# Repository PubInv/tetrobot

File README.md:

# gluss
An attempt to build metamorphic robots based on linear actuators. You probably want to go [https://pubinv.github.io/tetrobot/](https://pubinv.github.io/tetrobot/) first.

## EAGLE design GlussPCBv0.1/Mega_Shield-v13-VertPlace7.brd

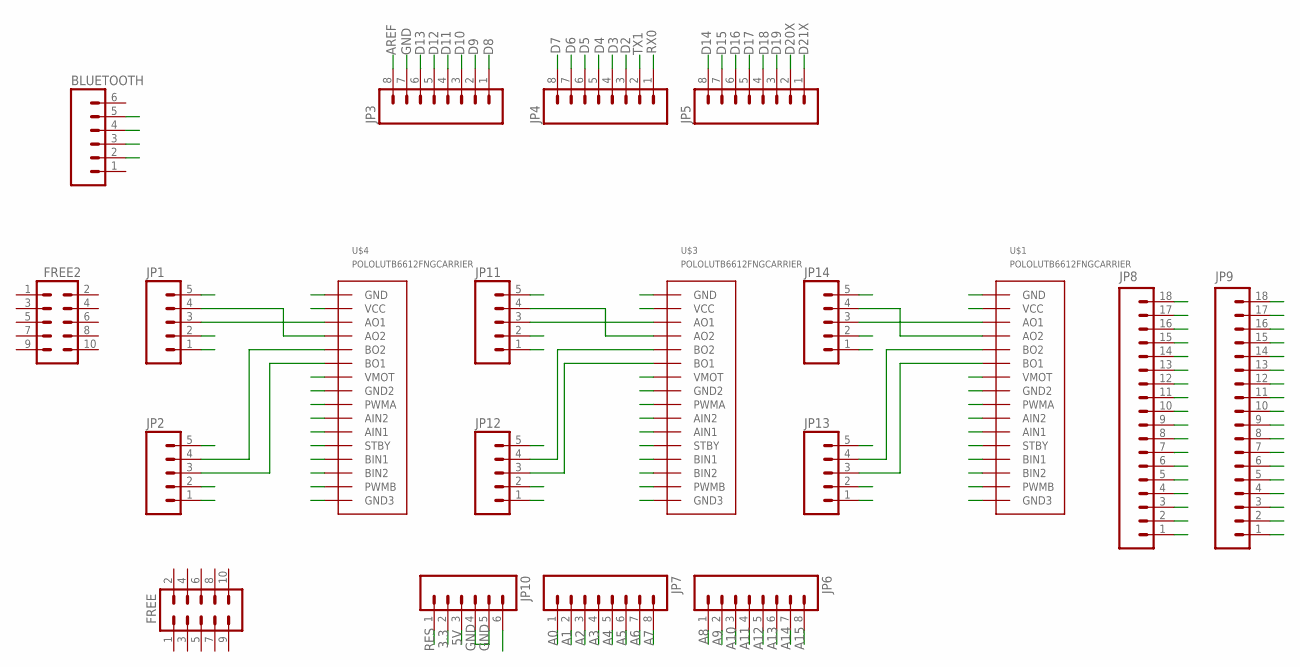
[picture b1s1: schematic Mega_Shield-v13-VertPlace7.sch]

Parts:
BLUETOOTH: M06FEMALE_LOCK; 1X06_FEMALE_LOCK.010
FREE, FREE2: M05X2NO_SILK; 2X5_NOSILK
JP1, JP2, JP11, JP12, JP13, JP14: M05LOCK; 1X05_LOCK
JP3, JP4, JP5, JP6, JP7: M08LOCK; 1X08_LOCK
JP8, JP9: M18_; 1X18
JP10: M06LOCK; 1X06_LOCK
U$1, U$3, U$4: POLOLUTB6612FNGCARRIER; THROUGHHOLECARRIER

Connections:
3.3: JP10.2
5V: BLUETOOTH.5, JP1.5, JP2.5, JP8.18, JP9.18, JP10.3, JP11.5, JP12.5, JP13.5, JP14.5, U$1.2 (VCC), U$1.12 (STBY), U$3.2 (VCC), U$3.12 (STBY), U$4.2 (VCC), U$4.12 (STBY)
A0: JP7.1, JP14.2
A1: JP7.2, JP13.2
A2: JP7.3, JP11.2
A3: JP7.4, JP12.2
A4: JP1.2, JP7.5
A5: JP2.2, JP7.6
A6: JP7.7
A7: JP7.8
A8: JP6.1
A9: JP6.2
A10: JP6.3
A11: JP6.4
A12: JP6.5
A13: JP6.6
A14: JP6.7
A15: JP6.8
AREF: JP3.8
D2: JP4.3, U$1.9 (PWMA)
D3: JP4.4, U$1.15 (PWMB)
D4: JP4.5, U$3.9 (PWMA)
D5: JP4.6, U$3.15 (PWMB)
D6: JP4.7, U$4.9 (PWMA)
D7: JP4.8, U$4.15 (PWMB)
D8: JP3.1
D9: JP3.2
D10: JP3.3
D11: JP3.4
D12: BLUETOOTH.2, JP3.5
D13: BLUETOOTH.3, JP3.6
D14: JP5.8
D15: JP5.7
D16: JP5.6
D17: JP5.5
D18: JP5.4
D19: JP5.3
D20X: JP5.2
D21X: JP5.1
D22: JP8.17
D23: JP9.17
D24: JP8.16
D25: JP9.16
D26: JP8.15
D27: JP9.15
D28: JP8.14
D29: JP9.14
D30: JP8.13
D31: JP9.13
D32: JP8.12
D33: JP9.12
D34: JP8.11
D35: JP9.11
D36: JP8.10
D37: JP9.10
D38: JP8.9
D40: JP8.8
D41: JP9.8
D42: JP8.7, U$4.14 (BIN2)
D43: JP9.7, U$4.13 (BIN1)
D44: JP8.6, U$4.10 (AIN2)
D45: JP9.6, U$4.11 (AIN1)
D46: JP8.5, U$3.14 (BIN2)
D47: JP9.5, U$3.13 (BIN1)
D48: JP8.4, U$3.10 (AIN2)
D49: JP9.4, U$3.11 (AIN1)
D50: JP8.3, U$1.14 (BIN2)
D51: JP9.3, U$1.13 (BIN1)
D52: JP8.2, U$1.10 (AIN2)
D53: JP9.2, U$1.11 (AIN1)
GND: BLUETOOTH.4, JP1.1, JP2.1, JP3.7, JP8.1, JP9.1, JP10.4, JP10.5, JP11.1, JP12.1, JP13.1, JP14.1, U$1.1 (GND), U$1.8 (GND2), U$1.16 (GND3), U$3.1 (GND), U$3.8 (GND2), U$3.16 (GND3), U$4.1 (GND), U$4.8 (GND2), U$4.16 (GND3)
unnamed: JP14.3, U$1.3 (AO1)
unnamed: JP14.4, U$1.4 (AO2)
unnamed: JP13.3, U$1.6 (BO1)
unnamed: JP13.4, U$1.5 (BO2)
unnamed: JP11.3, U$3.3 (AO1)
unnamed: JP12.3, U$3.6 (BO1)
unnamed: JP12.4, U$3.5 (BO2)
unnamed: JP11.4, U$3.4 (AO2)
unnamed: JP1.3, U$4.3 (AO1)
unnamed: JP1.4, U$4.4 (AO2)
unnamed: JP2.3, U$4.6 (BO1)
unnamed: JP2.4, U$4.5 (BO2)
RES: JP10.1
RX0: JP4.1
TX1: JP4.2
VIN: JP10.6, U$1.7 (VMOT), U$3.7 (VMOT), U$4.7 (VMOT)

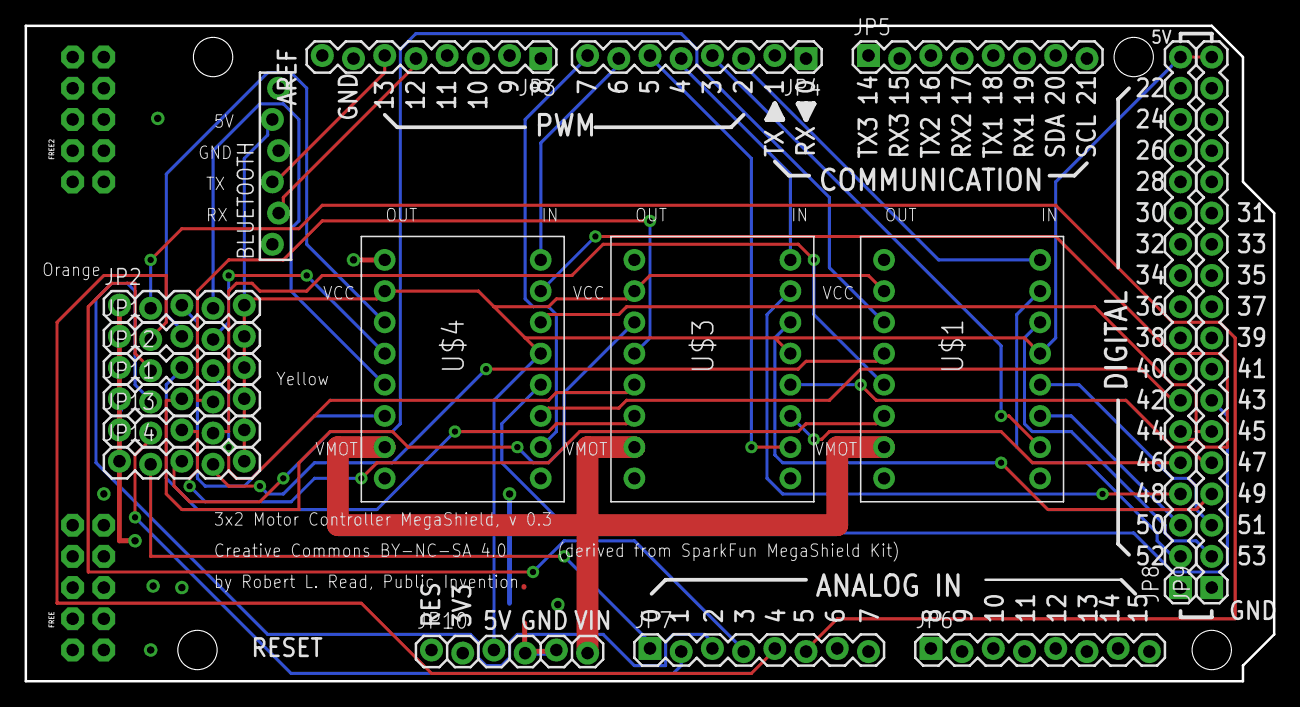
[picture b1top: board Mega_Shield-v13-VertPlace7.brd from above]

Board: 2 copper layers, 101.6 x 53.3 mm, 20 parts (0 on the bottom side), 41 nets.

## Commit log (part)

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2015-12-17 initial code for Arduino Mega
2015-12-20 finally have pure bluetooth working
2015-12-20 got the multiple thing working
2016-01-13 significant improvement
2016-01-13 more robust code to handle failing actuators
2016-03-01 Adding latest driver file, Makefile, Emacs Lisp control file, and bracket 3D printer files
2016-03-02 initial debug version of lisp interpreation of arduino output working
2016-03-02 improvements in status reporting and robustness of processing
2016-03-03 serious progress on simple s-expr library
2016-03-03 trying to move S-Expr
2016-03-04 supporing individual movement
2016-03-04 adding small example of positional operation
2016-03-05 significant progress on command convenience
2016-03-05 adding unique ids to calls and becoming more LISPy
2016-03-06 AWESOME--dance routine now allows series of steps across multiple controllers
2016-03-07 working through bug in value_i in S-Expr
2016-03-07 trying to get p function to work properly
2016-03-09 trouble with magit
2016-03-09 latest changes
2016-03-09 Test commit
2016-03-09 trivial change
2016-03-09 problems with magit
2016-03-09 drastic improvements to the way status is handeld
2016-03-10 New Poses
2016-03-10 adding .gitignore for Arduino complilation
2016-03-10 commiting pose
2016-03-11 adding scad
2016-03-11 new battery holder, first draft
2016-03-11 lots of movement but not walking, electronically buggy
2016-03-17 Forgot to actualy call del, now fixed!
2016-03-17 now walking, but very poorly
2016-03-18 Increaing baud rate to 19200, can't seem to go higher
2016-03-19 Major Milestone: move-forward now moves forward about 6" in 90 seconds
2016-03-20 turing left now works, although poorly
2016-03-20 added mirror function, though have not broadly employed it yet.
2016-03-23 fixing silly mistakes in mirroring
2016-03-24 mirorring working and turning working beautifully (45 degrees)
2016-03-24 slightly better move-forward routine
2016-03-24 slight improvements to walking
2016-03-24 major progress
2016-04-12 Create gh-pages branch via GitHub
2016-04-12 referencing public site
2016-04-12 updating before move to gh-pages
2016-04-12 removing gcoce from git control
2016-04-12 initial publication; half-baked
2016-04-13 Lots improvements
2016-04-14 improving photos and adding reference to issues
2016-04-15 Adding Table of Contents
2016-04-15 forgot to add this
2016-04-15 adding issues
2016-04-16 adding Eagle Files
2016-04-20 minor improvements
2016-04-20 changing to jekyll
2016-04-20 Touching
2016-04-20 adding empty
2016-04-20 yeah boy
2016-04-20 remvoing obsolete file
2016-04-20 fixing repo;
2016-04-20 tweak
2016-04-21 tweak spelling
2016-04-21 creating liquid variables
2016-04-21 teak
2016-04-30 tweaking link
2016-05-02 good progress on technical paper
2016-05-02 whoops, removing bad files
2016-05-04 significant work
2016-05-04 adding enclosures
2016-05-09 addition done
2016-05-09 trying to add back
2016-05-09 removing bad files
2016-05-09 adding link
2016-05-10 adding tensegrity info
2016-05-10 adding map for reconstruction
2016-05-11 creating a draft on wavelets
2016-05-11 adding
2016-05-11 wavelet algorithm
2016-05-25 adding js files
2016-05-25 adding playground
2016-05-25 sprites working
2016-05-26 significant improvements in constraints
2016-05-26 resizing better, executable code added
2016-05-27 name collision
2016-05-27 slight rewrite
2016-06-21 minor
2016-06-21 latest
2016-07-08 significant improvements in the sprite handling
2016-07-08 realistic physical model
2016-07-09 got actuator mapping stuff done
2016-07-13 rectify function and other improvements
2016-07-13 some more blind stabs in the dark
2016-07-14 new actuator numbering scheme
2016-07-15 allowing poses to be loaded
2016-07-15 adding pose for flat5
2016-07-19 render made more lisp compatible
2016-07-19 new functions
2016-07-19 can now execute gaits
2016-07-20 sideways walking seems to work
2016-07-20 broadwalk at 2.5mm/s
2016-07-20 can now move counter clock wise
2016-07-21 additions of battery/arduino enclusure
2016-07-21 adding combined_enclosure
2016-07-21 added two weird poses
2016-07-23 skinnywalk working a bit
2016-07-28 combined enclosure
2016-07-28 skinny walk working a little better
2016-07-28 clockwise turn pretty nice
2016-08-14 increasing timeout
2016-08-15 thinwalk
2016-08-15 move to 5tetglussbot
2016-08-15 improvement
2016-08-15 go ahead
2016-08-17 adding some picture
2016-08-19 udpate
2016-08-21 rearranging figures
2016-08-21 Changing Figures
2016-08-21 GlussRAM added for submission
2016-09-07 updating pdf with typos fixed
2016-09-11 adding the art
2016-09-11 robot
2016-09-11 moved art
2016-09-11 trying new url
2016-09-11 adding title
2016-09-11 trying to add title
2016-09-12 adding art
2016-09-12 adding abstract
2016-09-12 adding link to Wanted Hero
2016-09-12 minor tweaks
2016-09-12 proofreading
2016-09-13 lowres versions
2016-09-13 final for submission
2016-09-13 changing href to url
2016-09-13 further tweaks
2016-09-13 additional tweaks
2016-09-13 final as submitted
2016-09-16 spelling mistakes
2016-09-19 attempt to create Facebook App, might back this out
2016-09-19 layout
2016-09-19 a little new
2016-09-19 moving button
2016-09-19 yet another tweak
2016-09-19 moving button again
2016-09-19 changing title
2016-09-20 adding league facebook beginning
2016-09-20 league
2016-09-20 remove
2016-10-21 sending poses to url
2016-10-21 significant improvements in opening web server to simulation
2016-10-21 working nicely in sending data to robot
2016-10-24 removing weird color change
2016-10-27 adding new reference
2016-10-28 adding boostrap, reorgs
2016-10-28 allowing named poses to be reached as buttons
2016-11-09 some improvements in web-server
2016-11-09 working on test
2016-11-11 adding axes
2016-11-11 thickened lines
2016-11-11 adding first standard_gait
2016-11-11 playground
2016-11-11 adding ability to produce JSON
2016-11-11 can load standard gaits, but they are not working well
2016-11-12 Some of the gaits working with change in shape for friction
2016-11-14 memory leak fixed, but still slows down
2016-11-14 significant performance improvements
2016-11-15 major performance improvements, need to rethink now
2016-11-15 tiny fix
2016-11-15 standard
2016-11-15 adding commas
2016-11-15 adding quotes
2016-11-16 tested code to execute the GLOG more completely, but not integrated
2016-11-16 got exectution of GLOGs working
2016-11-16 major bugs fixed
2016-11-17 final on this weird branch
2016-11-19 addition of member objects has mostly broken locomotion, will fix soon
2016-11-19 working on adding second set of member constraints
2016-11-23 different approach to constraints
2016-11-26 fixed constraint problem (needs refactoring.)
2016-11-26 Still do not really have friction working with new objects
2016-11-26 friction working with new system but very poorly
2016-11-28 cleaned up sprites
2016-11-28 improving constraints handling a bit
2016-11-28 fixing endpoints
2016-11-28 obstacles form a pen
2016-11-29 phase 2 of mirroredWorld
2016-11-29 phase 3 of global variable refactoring
2016-11-29 phase 4 of global refactoring
2016-11-30 most globals removed
2016-11-30 further improvements
2016-11-30 working on localization
2016-11-30 used forEach in many instances, but not done
2016-11-30 some compactification
2016-11-30 further clean up
2016-12-01 some more improvement
2016-12-01 yet some more changes
2016-12-01 better use of object names
2016-12-01 adding axes.js
2016-12-01 avoiding erroneous send to robot
2016-12-01 changes to physics
2016-12-01 improving resizing
2016-12-02 improving collision detection
2016-12-03 potential improvement by moving mesh generation
2016-12-05 first attempt at integrating ammo physcis engine
2016-12-06 obstacles added, but before mouse-grab work
2016-12-06 Ammo world encapsulated in object
2016-12-06 some progress getting grabbing to work
2016-12-07 progress but lots of problems
2016-12-07 finally grabbing is partially working
2016-12-07 finally making some sense
2016-12-07 some progress on adding robot
2016-12-07 members added, but not constraints
2016-12-08 Robot constraints now present, use rather awkward
2016-12-09 added ability to control gravity of individual item
2016-12-09 initial code for probing gluss-con
2016-12-09 minor improvements in event handling
2016-12-09 significant GUI improvements
2016-12-10 some improvements, many bugs remaining
2016-12-10 distance added to ammo
2016-12-10 continued progress switching to AMMO, but terrible bugs remaining
2016-12-12 tiny refactoring
2016-12-12 FINALLY, have grabbing of obstacles working based on inversion of transform, though had to do it in THREE.js
2016-12-12 improved damping
2016-12-12 better damping
2016-12-12 minor refactoring
2016-12-13 playing with Sphere
2016-12-13 jitter much better with sphere, but apparently no damping or friction on objects
2016-12-13 weird but working solution to the rolling sphere problem
2016-12-13 minor fix to camera
2016-12-14 considerable progress in object accuracy, poses not working
2016-12-15 improvement in color
2016-12-15 major memory leak fixed
2016-12-16 recompiled ammo.js
2016-12-16 sprites back in place
2016-12-16 sprites
2016-12-16 major dead code removed
2016-12-16 disabled force manipulation better
2016-12-18 removed some Cannon stuff
2016-12-18 sorty have dragging working better
2016-12-18 further cleanup
2016-12-18 shift key now locking elements (but needs color change).
2017-01-05 textual shift
2017-01-05 zeroing axes
2017-01-05 removing comments
2017-01-05 changing color of locked nodes
2017-01-09 tweaks to work with GlussCon
2017-01-18 bug fixes
2017-01-20 minor fix but still many problems
2017-01-20 allowing parameters on constraints
2017-01-21 some improvements in locking of nodes
2017-01-23 bringing documentation up to date
2017-01-23 changing from Ricker Wavelet to Haar Wavelet
2017-01-26 adding tetrabeam pose
2017-01-27 equitetrabeam working, but chirality confused
2017-01-28 some progress, proof awful, needs screenshots.
2017-01-28 adding some patents to properly cite
2017-01-28 started to do better coloring, colors not retained!
2017-01-28 significant improvement on the proof
2017-01-29 Tetrahelix twisting figures
2017-01-29 some loose notes added
2017-01-29 minor tweaks to the Equitetrabeam
2017-01-30 proof sketch idea for closed-form generating expression added
2017-01-31 adding generateTetrahelix.js
2017-01-31 adding equitetrabeam stuff for now
2017-02-02 continuous helix for each rail worked out
2017-02-02 parametrization working
2017-02-02 corrections
2017-02-03 diagram improvements
2017-02-04 hello
2017-02-04 committing
2017-02-04 new, more general proofs
2017-02-05 generalization of formula
2017-02-05 Removing proof of Equitetrabeam in hopes more general formula functions
2017-02-06 tweaks
2017-03-04 equitetrabeam working better
2017-03-05 got delta vector computations partially working
2017-03-06 latest approach
2017-03-06 improvements in apply_delta_pose
2017-03-08 not very useful attempts to make it easier to design walking
2017-03-08 slightly better glusscon management
2017-03-16 initial progress on using TaskScheduler
2017-03-17 progress, but messed up
2017-03-18 finally got the interactive time down to less than 500 milliseconds
2017-03-18 finally working pretty well!
2017-03-23 obsolete but updating
2017-04-01 equitetrabeam working, but ability to manipulate awful
2017-04-04 significatn progress on abstract robot
2017-04-05 before my attempt to swizzle to the getter and setter on the nodes, to remove use of bullet for the physical robot only
2017-04-07 adding new numbering
2017-04-07 major subtle bug fixed
2017-04-22 some bug fixes and extra functions that made gait work
2017-04-25 ready for merge
2017-04-26 some new functions
2017-04-27 preparing for attempt to use Cassowary.js
2017-04-27 adding cassowary
2017-04-27 readding robot
2017-05-11 bringing more up-to-date
2017-05-11 syntax fix
2017-05-13 removing glussbot name
2017-05-13 changing name
2017-08-11 fixing link
2018-02-06 initial attempt to make call to the virtual world (C++)
2018-02-07 can now connect to the C++ world

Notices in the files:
GlussPCBv0.1/Mega_Shield-v13-VertPlace7.brd:
Creative Commons BY-NC-SA 4.0
parts and their libraries:
SparkFun-Connectors: Licensing: Creative Commons ShareAlike 4.0 International - https://creativecommons.org/licenses/by-sa/4.0
